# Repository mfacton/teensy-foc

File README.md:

# teensy-foc
Five Channel Teensy FOC Controller

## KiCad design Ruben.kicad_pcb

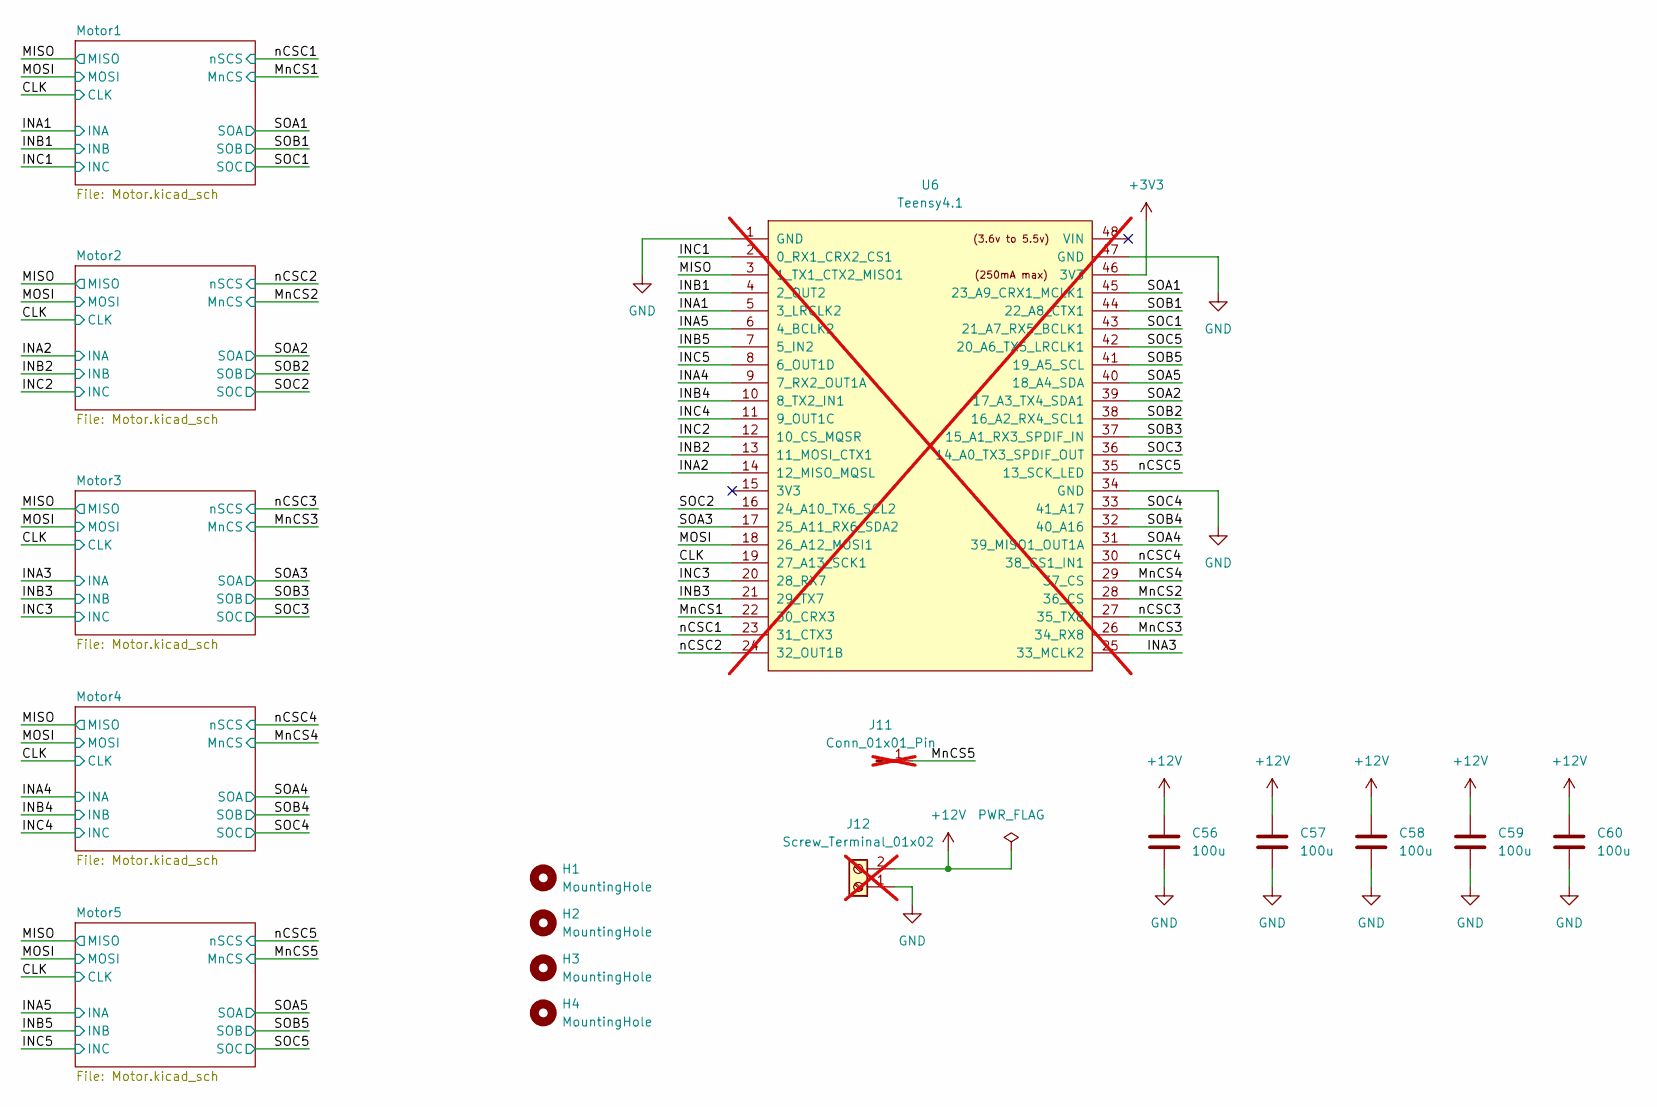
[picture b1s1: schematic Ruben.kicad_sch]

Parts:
C56, C57, C58, C59, C60: 100u; C_Elec_8x6.2; LCSC C178539
H1, H2, H3, H4: MountingHole; MountingHole_2.2mm_M2
J11: Conn_01x01_Pin; PinHeader_1x01_P2.00mm_Vertical; not fitted
J12: Screw_Terminal_01x02; Conn_Screw_P2-6.35; not fitted
U6: Teensy4.1; Teensy41; not fitted

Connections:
+3V3: U6.46 (3V3); also elsewhere on the board
+12V: C56.1, C57.1, C58.1, C59.1, C60.1, J12.2; also elsewhere on the board
/CLK: U6.19 (27_A13_SCK1); also elsewhere on the board
/INA1: U6.5 (3_LRCLK2); also elsewhere on the board
/INA2: U6.14 (12_MISO_MQSL); also elsewhere on the board
/INA3: U6.25 (33_MCLK2); also elsewhere on the board
/INA4: U6.9 (7_RX2_OUT1A); also elsewhere on the board
/INA5: U6.6 (4_BCLK2); also elsewhere on the board
/INB1: U6.4 (2_OUT2); also elsewhere on the board
/INB2: U6.13 (11_MOSI_CTX1); also elsewhere on the board
/INB3: U6.21 (29_TX7); also elsewhere on the board
/INB4: U6.10 (8_TX2_IN1); also elsewhere on the board
/INB5: U6.7 (5_IN2); also elsewhere on the board
/INC1: U6.2 (0_RX1_CRX2_CS1); also elsewhere on the board
/INC2: U6.12 (10_CS_MQSR); also elsewhere on the board
/INC3: U6.20 (28_RX7); also elsewhere on the board
/INC4: U6.11 (9_OUT1C); also elsewhere on the board
/INC5: U6.8 (6_OUT1D); also elsewhere on the board
/MISO: U6.3 (1_TX1_CTX2_MISO1); also elsewhere on the board
/MOSI: U6.18 (26_A12_MOSI1); also elsewhere on the board
/MnCS1: U6.22 (30_CRX3); also elsewhere on the board
/MnCS2: U6.28 (36_CS); also elsewhere on the board
/MnCS3: U6.26 (34_RX8); also elsewhere on the board
/MnCS4: U6.29 (37_CS); also elsewhere on the board
/MnCS5: J11.1; also elsewhere on the board
/SOA1: U6.45 (23_A9_CRX1_MCLK1); also elsewhere on the board
/SOA2: U6.39 (17_A3_TX4_SDA1); also elsewhere on the board
/SOA3: U6.17 (25_A11_RX6_SDA2); also elsewhere on the board
/SOA4: U6.31 (39_MISO1_OUT1A); also elsewhere on the board
/SOA5: U6.40 (18_A4_SDA); also elsewhere on the board
/SOB1: U6.44 (22_A8_CTX1); also elsewhere on the board
/SOB2: U6.38 (16_A2_RX4_SCL1); also elsewhere on the board
/SOB3: U6.37 (15_A1_RX3_SPDIF_IN); also elsewhere on the board
/SOB4: U6.32 (40_A16); also elsewhere on the board
/SOB5: U6.41 (19_A5_SCL); also elsewhere on the board
/SOC1: U6.43 (21_A7_RX5_BCLK1); also elsewhere on the board
/SOC2: U6.16 (24_A10_TX6_SCL2); also elsewhere on the board
/SOC3: U6.36 (14_A0_TX3_SPDIF_OUT); also elsewhere on the board
/SOC4: U6.33 (41_A17); also elsewhere on the board
/SOC5: U6.42 (20_A6_TX5_LRCLK1); also elsewhere on the board
/nCSC1: U6.23 (31_CTX3); also elsewhere on the board
/nCSC2: U6.24 (32_OUT1B); also elsewhere on the board
/nCSC3: U6.27 (35_TX8); also elsewhere on the board
/nCSC4: U6.30 (38_CS1_IN1); also elsewhere on the board
/nCSC5: U6.35 (13_SCK_LED); also elsewhere on the board
GND: C56.2, C57.2, C58.2, C59.2, C60.2, J12.1, U6.1 (GND), U6.34 (GND), U6.47 (GND); also elsewhere on the board

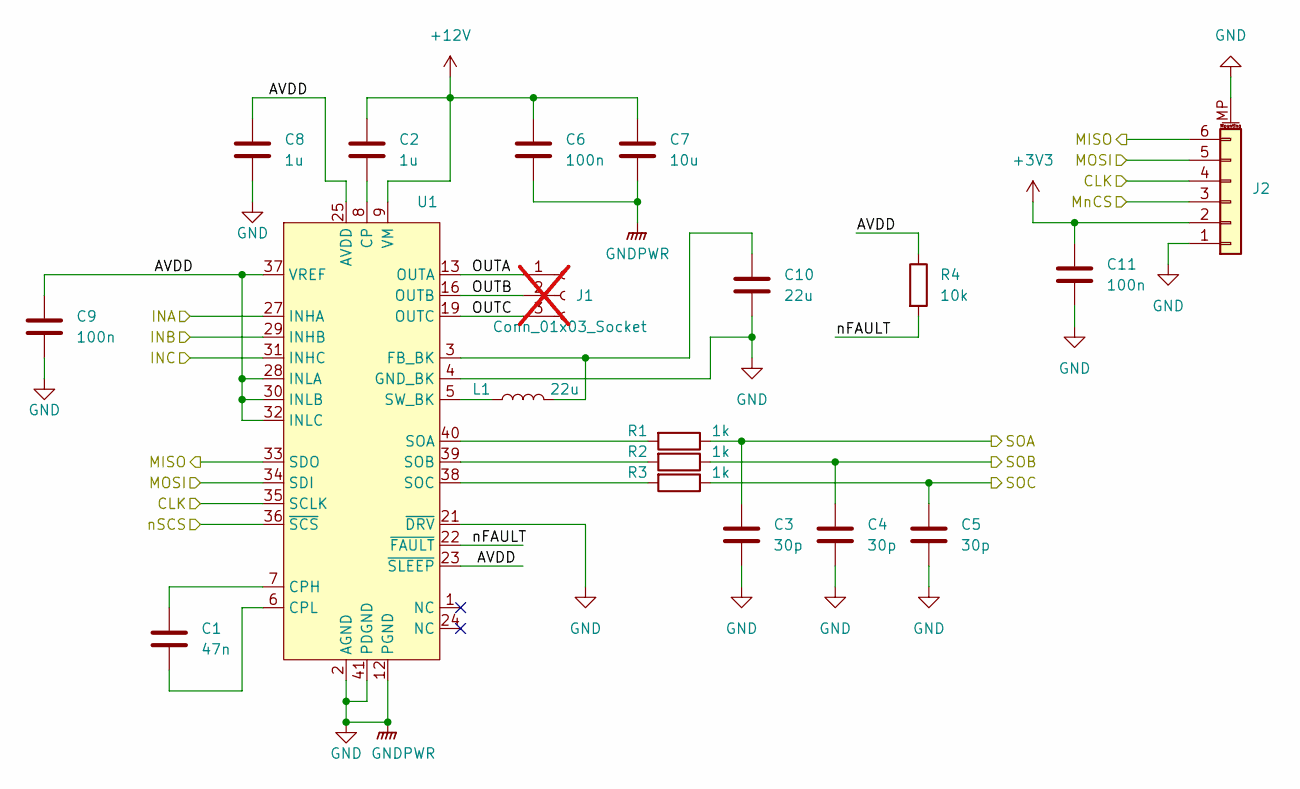
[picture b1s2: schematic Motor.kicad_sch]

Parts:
C1: 47n; C_0603_1608Metric
C2, C8: 1u; C_0402_1005Metric
C3, C4, C5: 30p; C_0402_1005Metric; LCSC C1570
C6, C9, C11: 100n; C_0402_1005Metric; LCSC C307331
C7: 10u; C_0603_1608Metric; LCSC C96446
C10: 22u; C_0603_1608Metric; LCSC C59461
J1: Conn_01x03_Socket; JST_XH_S3B-XH-A_1x03_P2.50mm_Horizontal; not fitted
J2: Conn_01x06_MountingPin; Molex_PicoBlade_53261-0671_1x06-1MP_P1.25mm_Horizontal; LCSC C99277
L1: 22u; L_0805_2012Metric; LCSC C32375
R1, R2, R3: 1k; R_0402_1005Metric; LCSC C11702
R4: 10k; R_0402_1005Metric; LCSC C25744
U1: VQFN-40

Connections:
+3V3: C11.2, J2.2; also elsewhere on the board
+12V: C2.2, C6.2, C7.2, U1.9 (VM), U1.10 (VM), U1.11 (VM); also elsewhere on the board
/CLK: J2.4, U1.35 (SCLK); also elsewhere on the board
/INA1: U1.27 (INHA); also elsewhere on the board
/INB1: U1.29 (INHB); also elsewhere on the board
/INC1: U1.31 (INHC); also elsewhere on the board
/MISO: J2.6, U1.33 (SDO); also elsewhere on the board
/MOSI: J2.5, U1.34 (SDI); also elsewhere on the board
/MnCS1: J2.3; also elsewhere on the board
/Motor1/AVDD: C8.2, C9.2, R4.1, U1.23 (~SLEEP), U1.25 (AVDD), U1.28 (INLA), U1.30 (INLB), U1.32 (INLC), U1.37 (VREF)
/Motor1/OUTA: J1.1, U1.13 (OUTA), U1.14 (OUTA)
/Motor1/OUTB: J1.2, U1.16 (OUTB), U1.17 (OUTB)
/Motor1/OUTC: J1.3, U1.19 (OUTC), U1.20 (OUTC)
/Motor1/nFAULT: R4.2, U1.22 (~FAULT)
/SOA1: C3.2, R1.1; also elsewhere on the board
/SOB1: C4.2, R2.1; also elsewhere on the board
/SOC1: C5.2, R3.1; also elsewhere on the board
/nCSC1: U1.36 (~SCS); also elsewhere on the board
GND: C3.1, C4.1, C5.1, C6.1, C7.1, C8.1, C9.1, C10.1, C11.1, J2.1, J2.MP (MountPin), U1.2 (AGND), U1.4 (GND_BK), U1.12 (PGND), U1.15 (PGND), U1.18 (PGND), U1.21 (~DRV), U1.26 (AGND), U1.41 (PDGND); also elsewhere on the board
unnamed: C2.1, U1.8 (CP)
unnamed: C1.2, U1.7 (CPH)
unnamed: C1.1, U1.6 (CPL)
unnamed: C10.2, L1.2, U1.3 (FB_BK)
unnamed: R1.2, U1.40 (SOA)
unnamed: R2.2, U1.39 (SOB)
unnamed: R3.2, U1.38 (SOC)
unnamed: L1.1, U1.5 (SW_BK)

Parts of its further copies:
C12, C16, C22, C23, C27, C33, C34, C38, C44, C45, C49, C55: 100n; C_0402_1005Metric; LCSC C307331
C13, C24, C35, C46: 47n; C_0603_1608Metric
C14, C15, C25, C26, C36, C37, C47, C48: 1u; C_0402_1005Metric
C17, C28, C39, C50: 10u; C_0603_1608Metric; LCSC C96446
C18, C20, C21, C29, C31, C32, C40, C42, C43, C51, C53, C54: 30p; C_0402_1005Metric; LCSC C1570
C19, C30, C41, C52: 22u; C_0603_1608Metric; LCSC C59461
J3, J5, J7, J9: Conn_01x03_Socket; JST_XH_S3B-XH-A_1x03_P2.50mm_Horizontal; not fitted
J4, J6, J8, J10: Conn_01x06_MountingPin; Molex_PicoBlade_53261-0671_1x06-1MP_P1.25mm_Horizontal; LCSC C99277
L2, L3, L4, L5: 22u; L_0805_2012Metric; LCSC C32375
R5, R6, R7, R9, R10, R11, R13, R14, R15, R17, R18, R19: 1k; R_0402_1005Metric; LCSC C11702
R8, R12, R16, R20: 10k; R_0402_1005Metric; LCSC C25744
U2, U3, U4, U5: VQFN-40

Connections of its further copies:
+3V3: C22.2, C33.2, C44.2, C55.2, J4.2, J6.2, J8.2, J10.2; also elsewhere on the board
+12V: C15.2, C16.2, C17.2, C26.2, C27.2, C28.2, C37.2, C38.2, C39.2, C48.2, C49.2, C50.2, U2.9 (VM), U2.10 (VM), U2.11 (VM), U3.9 (VM), U3.10 (VM), U3.11 (VM), U4.9 (VM), U4.10 (VM), U4.11 (VM), U5.9 (VM), U5.10 (VM), U5.11 (VM); also elsewhere on the board
/CLK: J4.4, J6.4, J8.4, J10.4, U2.35 (SCLK), U3.35 (SCLK), U4.35 (SCLK), U5.35 (SCLK); also elsewhere on the board
/INA2: U2.27 (INHA); also elsewhere on the board
/INA3: U3.27 (INHA); also elsewhere on the board
/INA4: U4.27 (INHA); also elsewhere on the board
/INA5: U5.27 (INHA); also elsewhere on the board
/INB2: U2.29 (INHB); also elsewhere on the board
/INB3: U3.29 (INHB); also elsewhere on the board
/INB4: U4.29 (INHB); also elsewhere on the board
/INB5: U5.29 (INHB); also elsewhere on the board
/INC2: U2.31 (INHC); also elsewhere on the board
/INC3: U3.31 (INHC); also elsewhere on the board
/INC4: U4.31 (INHC); also elsewhere on the board
/INC5: U5.31 (INHC); also elsewhere on the board
/MISO: J4.6, J6.6, J8.6, J10.6, U2.33 (SDO), U3.33 (SDO), U4.33 (SDO), U5.33 (SDO); also elsewhere on the board
/MOSI: J4.5, J6.5, J8.5, J10.5, U2.34 (SDI), U3.34 (SDI), U4.34 (SDI), U5.34 (SDI); also elsewhere on the board
/MnCS2: J4.3; also elsewhere on the board
/MnCS3: J6.3; also elsewhere on the board
/MnCS4: J8.3; also elsewhere on the board
/MnCS5: J10.3; also elsewhere on the board
/Motor2/AVDD: C12.2, C14.2, R8.1, U2.23 (~SLEEP), U2.25 (AVDD), U2.28 (INLA), U2.30 (INLB), U2.32 (INLC), U2.37 (VREF)
/Motor2/OUTA: J3.1, U2.13 (OUTA), U2.14 (OUTA)
/Motor2/OUTB: J3.2, U2.16 (OUTB), U2.17 (OUTB)
/Motor2/OUTC: J3.3, U2.19 (OUTC), U2.20 (OUTC)
/Motor2/nFAULT: R8.2, U2.22 (~FAULT)
/Motor3/AVDD: C23.2, C25.2, R12.1, U3.23 (~SLEEP), U3.25 (AVDD), U3.28 (INLA), U3.30 (INLB), U3.32 (INLC), U3.37 (VREF)
/Motor3/OUTA: J5.1, U3.13 (OUTA), U3.14 (OUTA)
/Motor3/OUTB: J5.2, U3.16 (OUTB), U3.17 (OUTB)
/Motor3/OUTC: J5.3, U3.19 (OUTC), U3.20 (OUTC)
/Motor3/nFAULT: R12.2, U3.22 (~FAULT)
/Motor4/AVDD: C34.2, C36.2, R16.1, U4.23 (~SLEEP), U4.25 (AVDD), U4.28 (INLA), U4.30 (INLB), U4.32 (INLC), U4.37 (VREF)
/Motor4/OUTA: J7.1, U4.13 (OUTA), U4.14 (OUTA)
/Motor4/OUTB: J7.2, U4.16 (OUTB), U4.17 (OUTB)
/Motor4/OUTC: J7.3, U4.19 (OUTC), U4.20 (OUTC)
/Motor4/nFAULT: R16.2, U4.22 (~FAULT)
/Motor5/AVDD: C45.2, C47.2, R20.1, U5.23 (~SLEEP), U5.25 (AVDD), U5.28 (INLA), U5.30 (INLB), U5.32 (INLC), U5.37 (VREF)
/Motor5/OUTA: J9.1, U5.13 (OUTA), U5.14 (OUTA)
/Motor5/OUTB: J9.2, U5.16 (OUTB), U5.17 (OUTB)
/Motor5/OUTC: J9.3, U5.19 (OUTC), U5.20 (OUTC)
/Motor5/nFAULT: R20.2, U5.22 (~FAULT)
/SOA2: C18.2, R5.1; also elsewhere on the board
/SOA3: C29.2, R9.1; also elsewhere on the board
/SOA4: C40.2, R13.1; also elsewhere on the board
/SOA5: C51.2, R17.1; also elsewhere on the board
/SOB2: C20.2, R6.1; also elsewhere on the board
/SOB3: C31.2, R10.1; also elsewhere on the board
/SOB4: C42.2, R14.1; also elsewhere on the board
/SOB5: C53.2, R18.1; also elsewhere on the board
/SOC2: C21.2, R7.1; also elsewhere on the board
/SOC3: C32.2, R11.1; also elsewhere on the board
/SOC4: C43.2, R15.1; also elsewhere on the board
/SOC5: C54.2, R19.1; also elsewhere on the board
/nCSC2: U2.36 (~SCS); also elsewhere on the board
/nCSC3: U3.36 (~SCS); also elsewhere on the board
/nCSC4: U4.36 (~SCS); also elsewhere on the board
/nCSC5: U5.36 (~SCS); also elsewhere on the board
GND: C12.1, C14.1, C16.1, C17.1, C18.1, C19.1, C20.1, C21.1, C22.1, C23.1, C25.1, C27.1, C28.1, C29.1, C30.1, C31.1, C32.1, C33.1, C34.1, C36.1, C38.1, C39.1, C40.1, C41.1, C42.1, C43.1, C44.1, C45.1, C47.1, C49.1, C50.1, C51.1, C52.1, C53.1, C54.1, C55.1, J4.1, J4.MP (MountPin), J6.1, J6.MP (MountPin), J8.1, J8.MP (MountPin), J10.1, J10.MP (MountPin), U2.2 (AGND), U2.4 (GND_BK), U2.12 (PGND), U2.15 (PGND), U2.18 (PGND), U2.21 (~DRV), U2.26 (AGND), U2.41 (PDGND), U3.2 (AGND), U3.4 (GND_BK), U3.12 (PGND), U3.15 (PGND), U3.18 (PGND), U3.21 (~DRV), U3.26 (AGND), U3.41 (PDGND), U4.2 (AGND), U4.4 (GND_BK), U4.12 (PGND), U4.15 (PGND), U4.18 (PGND), U4.21 (~DRV), U4.26 (AGND), U4.41 (PDGND), U5.2 (AGND), U5.4 (GND_BK), U5.12 (PGND), U5.15 (PGND), U5.18 (PGND), U5.21 (~DRV), U5.26 (AGND), U5.41 (PDGND); also elsewhere on the board
unnamed: C15.1, U2.8 (CP)
unnamed: C13.2, U2.7 (CPH)
unnamed: C13.1, U2.6 (CPL)
unnamed: C19.2, L2.2, U2.3 (FB_BK)
unnamed: R5.2, U2.40 (SOA)
unnamed: R6.2, U2.39 (SOB)
unnamed: R7.2, U2.38 (SOC)
unnamed: L2.1, U2.5 (SW_BK)
unnamed: C26.1, U3.8 (CP)
unnamed: C24.2, U3.7 (CPH)
unnamed: C24.1, U3.6 (CPL)
unnamed: C30.2, L3.2, U3.3 (FB_BK)
unnamed: R9.2, U3.40 (SOA)
unnamed: R10.2, U3.39 (SOB)
unnamed: R11.2, U3.38 (SOC)
unnamed: L3.1, U3.5 (SW_BK)
unnamed: C37.1, U4.8 (CP)
unnamed: C35.2, U4.7 (CPH)
unnamed: C35.1, U4.6 (CPL)
unnamed: C41.2, L4.2, U4.3 (FB_BK)
unnamed: R13.2, U4.40 (SOA)
unnamed: R14.2, U4.39 (SOB)
unnamed: R15.2, U4.38 (SOC)
unnamed: L4.1, U4.5 (SW_BK)
unnamed: C48.1, U5.8 (CP)
unnamed: C46.2, U5.7 (CPH)
unnamed: C46.1, U5.6 (CPL)
unnamed: C52.2, L5.2, U5.3 (FB_BK)
unnamed: R17.2, U5.40 (SOA)
unnamed: R18.2, U5.39 (SOB)
unnamed: R19.2, U5.38 (SOC)
unnamed: L5.1, U5.5 (SW_BK)

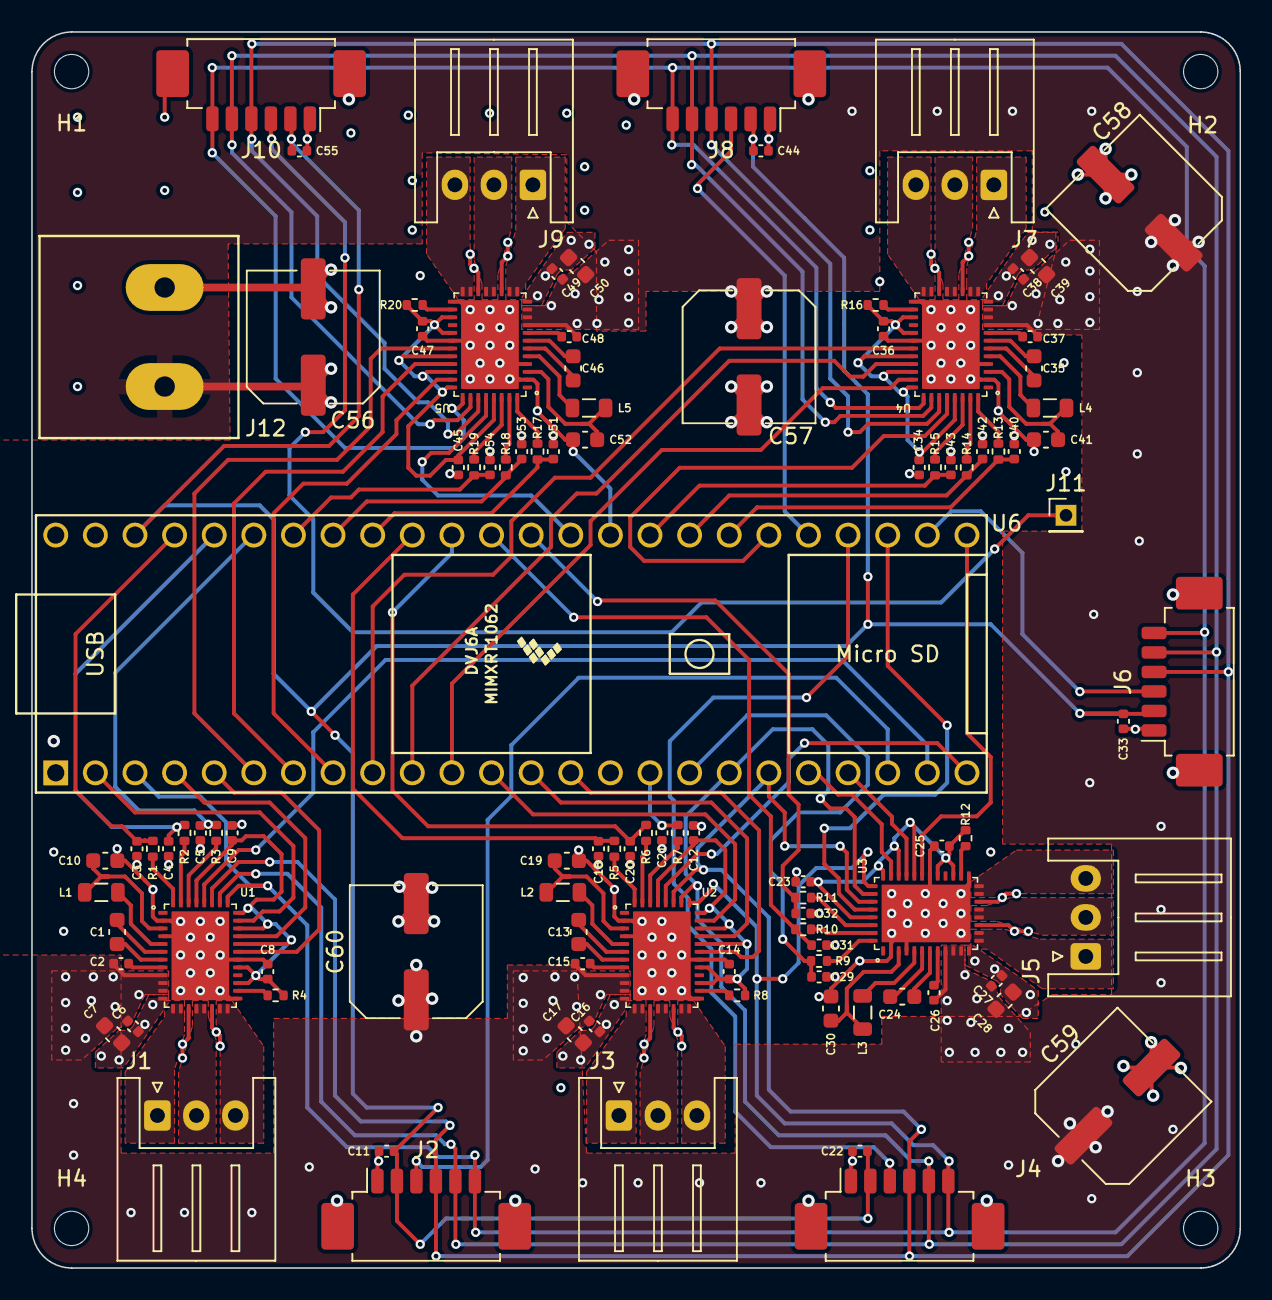
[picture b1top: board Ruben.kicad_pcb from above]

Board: 4 copper layers, 77.5 x 79.2 mm, 107 parts (0 on the bottom side), 111 nets.

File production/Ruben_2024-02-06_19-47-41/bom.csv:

Designator,Footprint,Quantity,Value,LCSC Part #
"C1, C13, C24, C35, C46",0603,5,47n,
"C10, C19, C30, C41, C52",0603,5,22u,
"C11, C12, C16, C22, C23, C27, C33, C34, C38, C44, C45, C49, C55, C6, C9",0402,15,100n,
"C14, C15, C2, C25, C26, C36, C37, C47, C48, C8",0402,10,1u,
"C17, C28, C39, C50, C7",0603,5,10u,
"C18, C20, C21, C29, C3, C31, C32, C4, C40, C42, C43, C5, C51, C53, C54",0402,15,30p,
"C56, C57, C58, C59, C60",C_Elec_8x6.2,5,100u,C178539
"J1, J3, J5, J7, J9",JST_XH_S3B-XH-A_1x03_P2.50mm_Horizontal,5,Conn_01x03_Socket,
"J10, J2, J4, J6, J8",Molex_PicoBlade_53261-0671_1x06-1MP_P1.25mm_Horizontal,5,Conn_01x06_Socket,
"L1, L2, L3, L4, L5",0805,5,22u,
"R1, R10, R11, R13, R14, R15, R17, R18, R19, R2, R3, R5, R6, R7, R9",0402,15,1k,
"R12, R16, R20, R4, R8",0402,5,10k,
"U1, U2, U3, U4, U5",VQFN-40,5,~,

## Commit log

2024-10-19 Transfer project
2024-10-19 Remove old production files
